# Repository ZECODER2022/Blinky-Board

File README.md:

# Planet Blinky Board 

My blinky board is the simple design that resembles a planet and its rings. It has 10 Leds arranged to blink in a circular pattern on the planet design. The Power input for it is on the back for easy to hide cable management to make it look cool.

**List of Parts:**
 - This project uses just the parts that come inside the hackclub blinky board bundle. For the PCB production it is estamated around $24.

**Photo of PCB design below:**

**Photo of Schemadic Below:**

This was my first ever custom PCB it came back with no issues when i ran a check and im pretty happy with how it came out!

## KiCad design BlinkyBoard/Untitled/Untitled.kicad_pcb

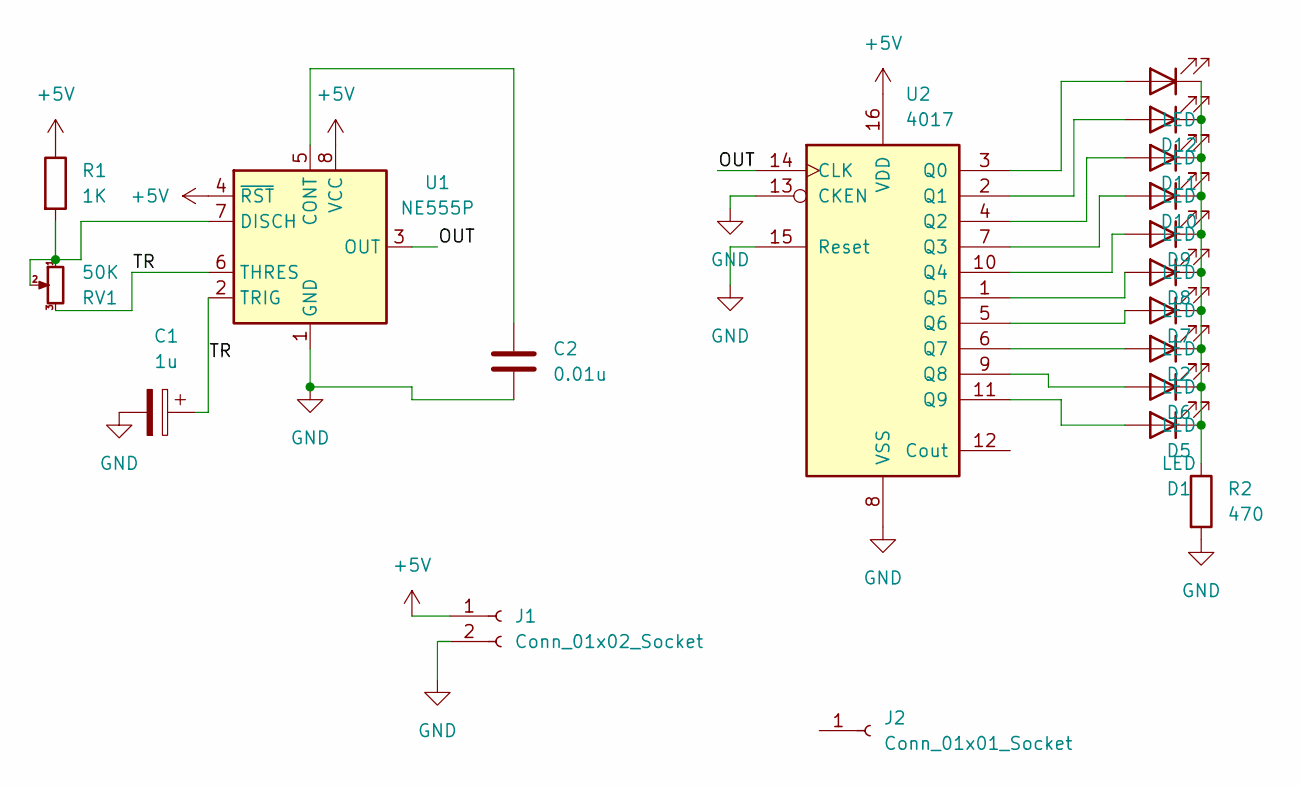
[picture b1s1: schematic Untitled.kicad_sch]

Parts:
C1: 1u; CP_Radial_D5.0mm_P2.00mm
C2: 0.01u; C_Disc_D7.5mm_W2.5mm_P5.00mm
D1, D2, D5, D6, D7, D8, D9, D10, D11, D12: LED; LED_D3.0mm
J1: Conn_01x02_Socket; PinHeader_1x02_P2.54mm_Vertical
J2: Conn_01x01_Socket; PinHeader_1x01_P2.54mm_Vertical
R1: 1K; R_Axial_DIN0207_L6.3mm_D2.5mm_P7.62mm_Horizontal
R2: 470; R_Axial_DIN0207_L6.3mm_D2.5mm_P7.62mm_Horizontal
RV1: 50K; Potentiometer_Vishay_T93YA_Vertical
U1: NE555P; DIP-8_W7.62mm
U2: 4017; N16

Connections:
+5V: J1.1, R1.1, U1.4 (~RST), U1.8 (VCC), U2.16 (VDD)
/OUT: U1.3 (OUT), U2.14 (CLK)
/TR: C1.1, RV1.3, U1.2 (TRIG), U1.6 (THRES)
GND: C1.2, C2.2, J1.2, R2.2, U1.1 (GND), U2.8 (VSS), U2.13 (CKEN), U2.15 (Reset)
unnamed: D1.2 (A), U2.11 (Q9)
unnamed: D1.1 (K), D2.1 (K), D5.1 (K), D6.1 (K), D7.1 (K), D8.1 (K), D9.1 (K), D10.1 (K), D11.1 (K), D12.1 (K), R2.1
unnamed: D2.2 (A), U2.5 (Q6)
unnamed: D5.2 (A), U2.9 (Q8)
unnamed: D6.2 (A), U2.6 (Q7)
unnamed: D7.2 (A), U2.1 (Q5)
unnamed: D8.2 (A), U2.10 (Q4)
unnamed: D9.2 (A), U2.7 (Q3)
unnamed: D10.2 (A), U2.4 (Q2)
unnamed: D11.2 (A), U2.2 (Q1)
unnamed: D12.2 (A), U2.3 (Q0)
unnamed: C2.1, U1.5 (CONT)
unnamed: R1.2, RV1.1, RV1.2, U1.7 (DISCH)

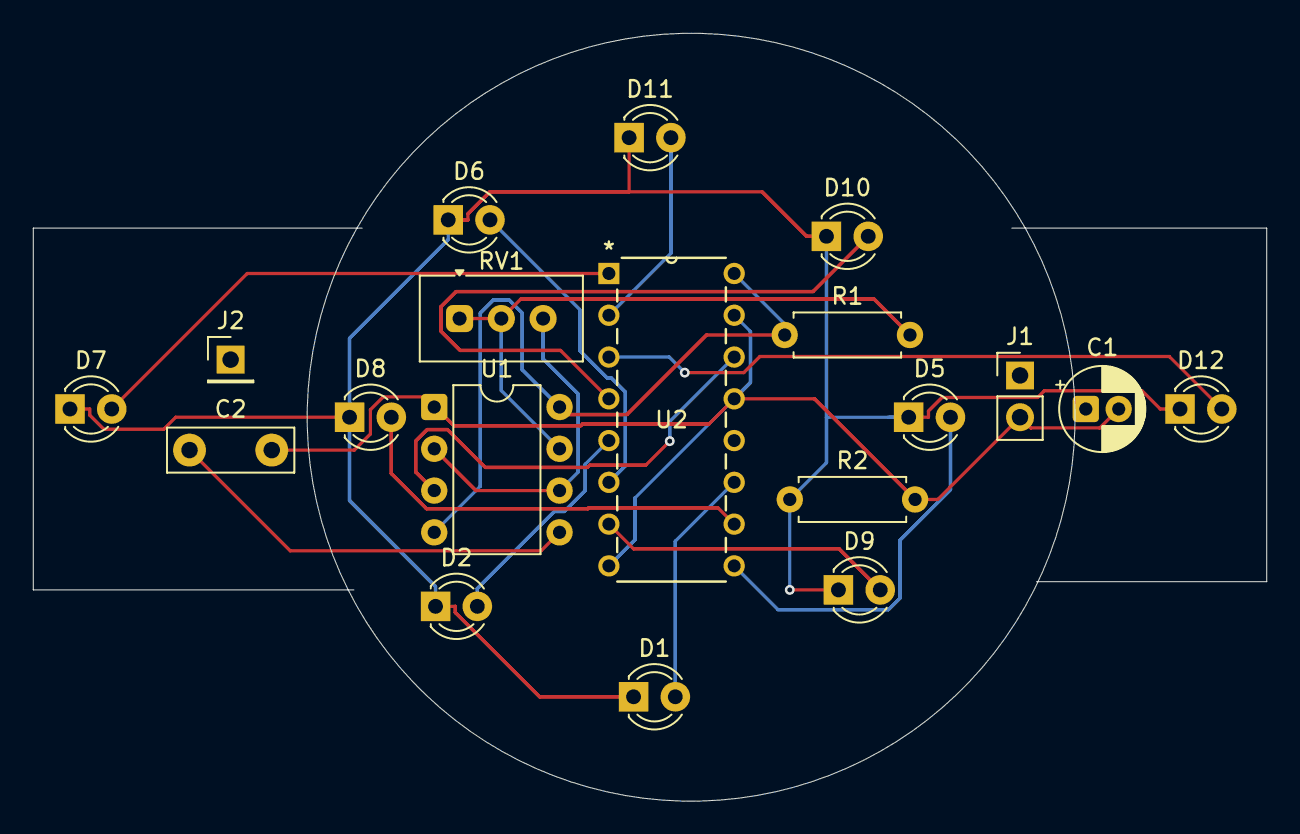
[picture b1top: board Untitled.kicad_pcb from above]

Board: 2 copper layers, 75.0 x 46.7 mm, 19 parts (0 on the bottom side), 17 nets.

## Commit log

2026-05-07 Revise README description of blinki board project
    Updated project description for clarity.
2026-05-07 added files
    I think I added the files
2026-05-07 added photo
2026-05-14 Revise README for Planet Blinky Board
    Updated project description and added parts list.
